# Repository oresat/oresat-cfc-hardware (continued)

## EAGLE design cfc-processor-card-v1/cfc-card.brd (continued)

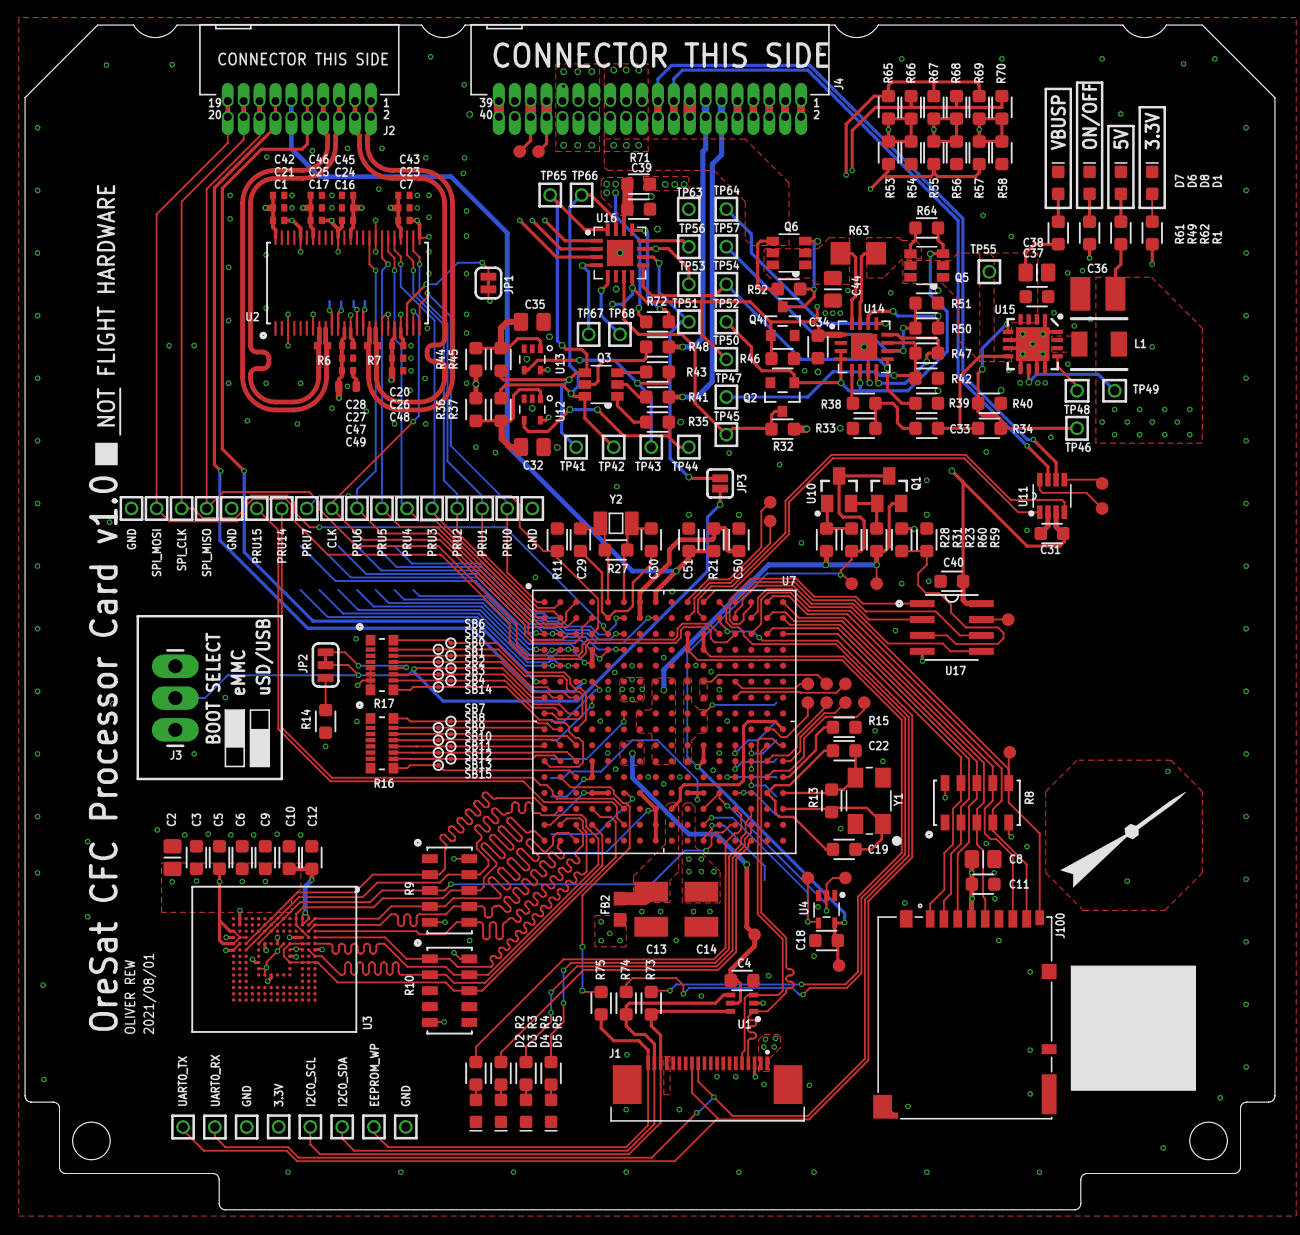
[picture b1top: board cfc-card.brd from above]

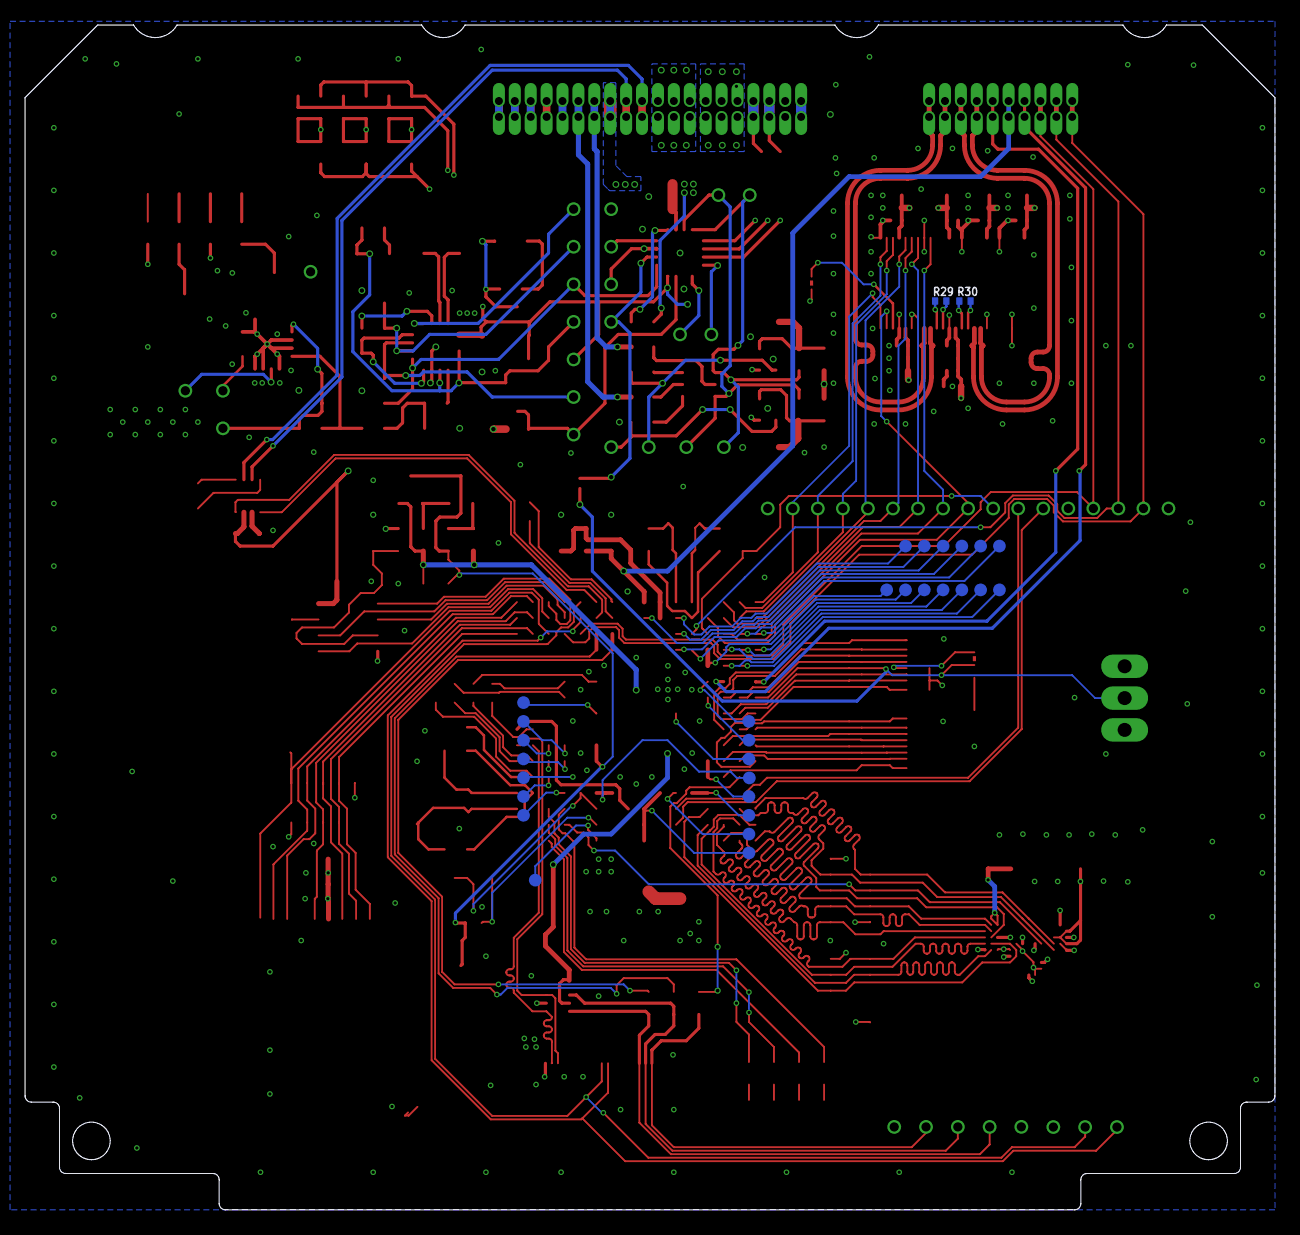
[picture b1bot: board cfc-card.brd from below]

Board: 4 copper layers, 99.8 x 94.6 mm, 274 parts (31 on the bottom side), 205 nets.

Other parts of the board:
U$2: CAMERA_BOARD_TOP_DIMS
U$3: PSAS_LOGO_10X10
U$4: ORESAT_ORIENTATION_COPPER

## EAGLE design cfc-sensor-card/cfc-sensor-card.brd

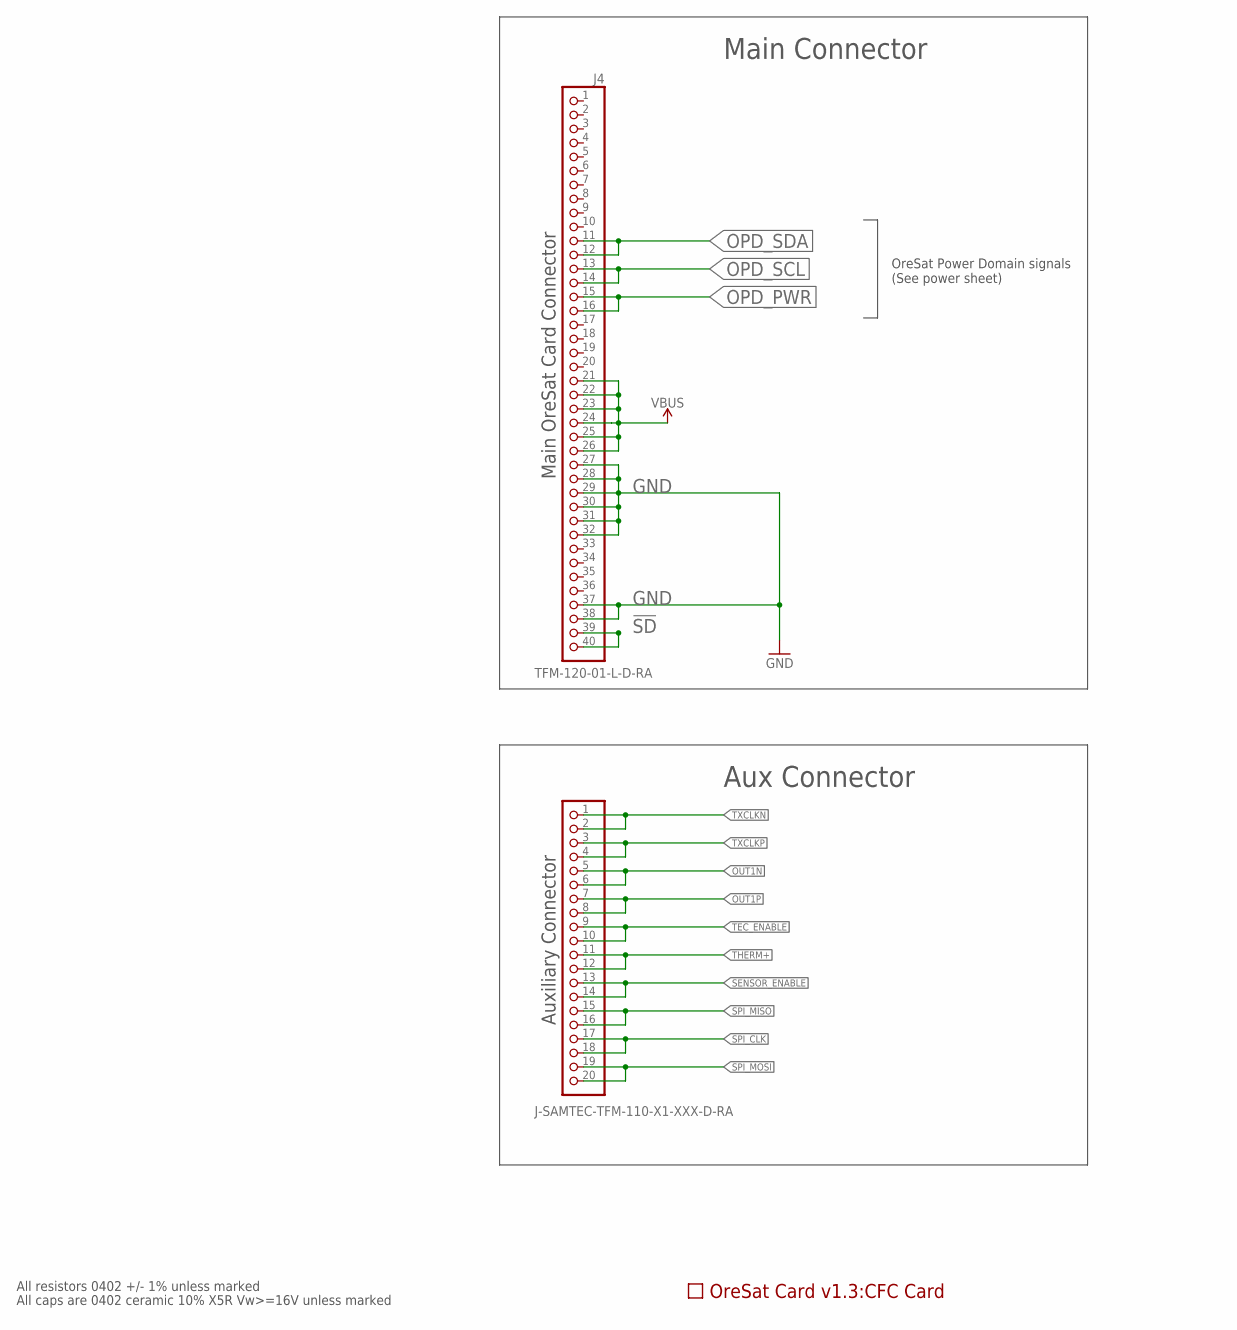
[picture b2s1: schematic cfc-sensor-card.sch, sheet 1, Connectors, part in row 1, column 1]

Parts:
J2: J-SAMTEC-TFM-110-X1-XXX-D-RA; MPN TFM-110-01-L-D-RA
J4: TFM-120-01-L-D-RA; J-SAMTEC-TFM-120-X1-XXX-D-RA
PCB1: ORESAT-CARD-V1.3-CFC
U$1: FLIGHMARKERNEW; FLIGHTMARKER_NEW_BOARDS

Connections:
!SD: J4.39, J4.40
GND: J4.27, J4.28, J4.29, J4.30, J4.31, J4.32, J4.37, J4.38; also elsewhere on the board
OPD_PWR: J4.15, J4.16; also elsewhere on the board
OPD_SCL: J4.13, J4.14; also elsewhere on the board
OPD_SDA: J4.11, J4.12; also elsewhere on the board
OUT1N: J2.5, J2.6; also elsewhere on the board
OUT1P: J2.7, J2.8; also elsewhere on the board
SENSOR_ENABLE: J2.13, J2.14; also elsewhere on the board
SPI_CLK: J2.17, J2.18; also elsewhere on the board
SPI_MISO: J2.15, J2.16; also elsewhere on the board
SPI_MOSI: J2.19, J2.20; also elsewhere on the board
TEC_ENABLE: J2.9, J2.10; also elsewhere on the board
THERM+: J2.11, J2.12; also elsewhere on the board
TXCLKN: J2.1, J2.2; also elsewhere on the board
TXCLKP: J2.3, J2.4; also elsewhere on the board
VBUS: J4.21, J4.22, J4.23, J4.24, J4.25, J4.26; also elsewhere on the board

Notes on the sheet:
OreSat Star Tracker: Connectors
1.2
All resistors 0402 +/- 1% unless marked
All caps are 0402 ceramic 10% X5R Vw>=16V unless marked
Main Connector
Main OreSat Card Connector
OreSat Power Domain signals (See power sheet)
Auxiliary Connector
Aux Connector

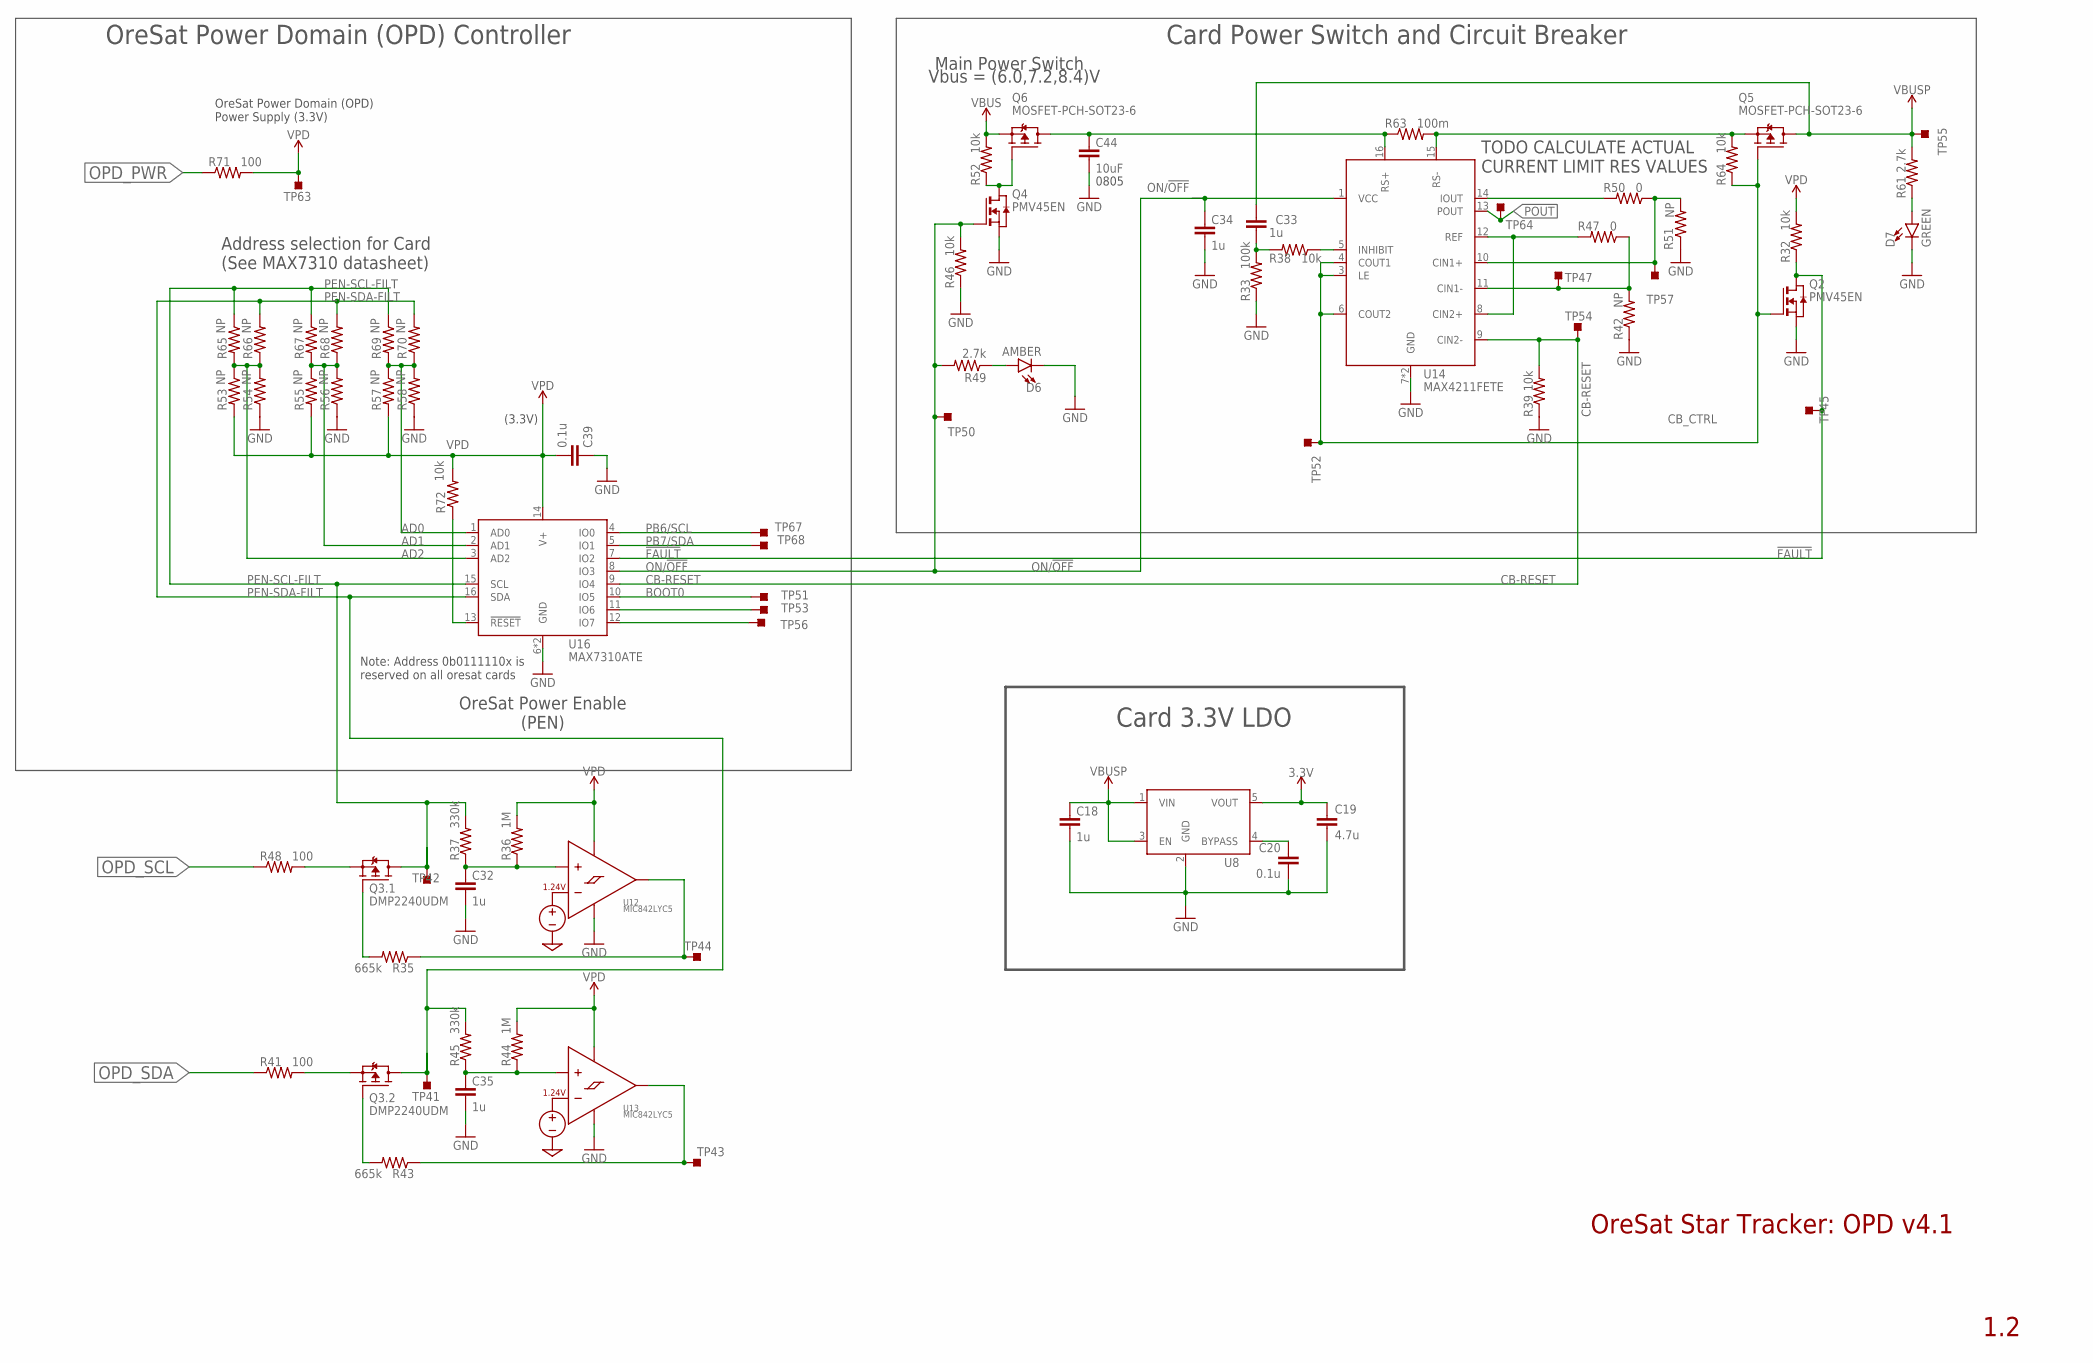
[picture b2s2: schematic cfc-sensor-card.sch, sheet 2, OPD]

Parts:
C18, C32, C33, C34, C35: 1u; .0603-B
C19: 4.7u; .0603-B
C20, C39: 0.1u; .0603-B
C44: 10uF; .0603-B
D6: AMBER; LED-0603
D7: GREEN; LED-0603
Q2, Q4: PMV45EN; SOT23; MPN PMV45EN2R
Q3: DMP2240UDM; SOT23-6
Q5, Q6: MOSFET-PCH-SOT23-6; SOT23-6; MPN DMP3050LVT-7
R32, R39, R46, R52, R64, R72: 10k; .0603-B
R33: 100k; .0603-B; MPN RC1005F6653CS
R35, R43: 665k; .0603-B
R36, R44: 1M; .0603-B
R37, R45: 330k; .0603-B
R38: 10k; .0603-B; MPN RC1005F6653CS
R41, R48, R71: 100; .0603-B
R42, R51, R53, R54, R55, R56, R57, R58, R65, R66, R67, R68, R69, R70: NP; .0603-B; MPN RC1005F6653CS
R47, R50: 0; .0603-B
R49, R61: 2.7k; .0603-B
R63: 100m; R1206
TP41, TP42, TP43, TP44, TP45, TP47, TP50, TP51, TP52, TP53, TP54, TP55, TP56, TP57, TP63, TP64, TP67, TP68: TEST-POINT_SMD-SMD-10SN; TESTPOINT_SMD-10SN
U8: LP2985AIM5-3.3_NOPB; SOT-23
U12, U13: MIC842LYC5; SC70-5
U14: MAX4211FETE; QFN65P400X400X80-17T210
U16: MAX7310ATE; QFN65P400X400X80-17T210; MPN MAX7310ATE

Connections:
3.3V: C19.1, U8.5 (VOUT); also elsewhere on the board
!FAULT: Q2.3 (D), R32.1, TP45.TP, U16.7 (IO2)
AD0: R57.1, R58.2, R69.2, R70.1, U16.1 (AD0)
AD1: R55.1, R56.2, R67.2, R68.1, U16.2 (AD1)
AD2: R53.1, R54.2, R65.2, R66.1, U16.3 (AD2)
BOOT0: TP51.TP, U16.10 (IO5)
CB-RESET: R39.2, TP54.TP, U14.9 (CIN2-), U16.9 (IO4)
CB_CTRL: Q2.1 (G), Q5.3 (G), R64.1, TP52.TP, U14.3 (LE), U14.4 (COUT1), U14.6 (COUT2)
GND: C18.2, C19.2, C20.2, C32.2, C34.2, C35.2, C39.1, C44.2, D6.C, D7.C, Q2.2 (S), Q4.2 (S), R33.1, R39.1, R42.1, R46.1, R51.1, R54.1, R56.1, R58.1, U8.2 (GND), U12.2 (GND), U13.2 (GND), U14.7 (GND), U14.EPAD (GND), U16.6 (GND), U16.EPAD (GND); also elsewhere on the board
IOUT: R50.2, U14.14 (IOUT)
unnamed: C20.1, U8.4 (BYPASS)
unnamed: C32.1, R36.1, R37.1, U12.1 (INP)
unnamed: R35.1, TP44.TP, U12.4 (OUT)
unnamed: TP56.TP, U16.12 (IO7)
unnamed: C44.1, Q6.1 (D), Q6.2 (D), Q6.5 (D), Q6.6 (D), R63.1, U14.16 (RS+)
unnamed: Q5.4 (S), R63.2, R64.2, U14.15 (RS-)
unnamed: C35.1, R44.1, R45.1, U13.1 (INP)
unnamed: Q3.3 (G), R43.2
unnamed: Q3.1 (G), R35.2
unnamed: D7.A, R61.1
unnamed: TP53.TP, U16.11 (IO6)
unnamed: Q3.5 (S), R48.2
unnamed: D6.A, R49.1
unnamed: Q3.2 (S), R41.2
unnamed: R43.1, TP43.TP, U13.4 (OUT)
unnamed: R72.1, U16.13 (!RESET)
unnamed: Q4.3 (D), Q6.3 (G), R52.1
unnamed: R50.1, R51.2, TP57.TP, U14.10 (CIN1+)
unnamed: R42.2, R47.1, TP47.TP, U14.11 (CIN1-)
unnamed: R47.2, U14.8 (CIN2+), U14.12 (REF)
unnamed: C33.1, R33.2, R38.2
unnamed: R38.1, U14.5 (INHIBIT)
ON/!OFF: C34.1, Q4.1 (G), R46.2, R49.2, TP50.TP, U14.1 (VCC), U16.8 (IO3)
OPD_PWR: R71.1; also elsewhere on the board
OPD_SCL: R48.1; also elsewhere on the board
OPD_SDA: R41.1; also elsewhere on the board
PB6/SCL: TP67.TP, U16.4 (IO0)
PB7/SDA: TP68.TP, U16.5 (IO1)
PEN-SCL-FILT: Q3.6 (D), R37.2, R65.1, R67.1, R69.1, TP42.TP, U16.15 (SCL)
PEN-SDA-FILT: Q3.4 (D), R45.2, R66.2, R68.2, R70.2, TP41.TP, U16.16 (SDA)
POUT: TP64.TP, U14.13 (POUT)
VBUS: Q6.4 (S), R52.2; also elsewhere on the board
VBUSP: C18.1, C33.2, Q5.1 (D), Q5.2 (D), Q5.5 (D), Q5.6 (D), R61.2, TP55.TP, U8.1 (VIN), U8.3 (EN); also elsewhere on the board
VPD: C39.2, R32.2, R36.2, R44.2, R53.2, R55.2, R57.2, R71.2, R72.2, TP63.TP, U12.5 (VDD), U13.5 (VDD), U16.14 (V+)

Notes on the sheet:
1.2
Main Power Switch
OreSat Power Enable (PEN)
Address selection for Card (See MAX7310 datasheet)
(3.3V)
Vbus = (6.0,7.2,8.4)V
OreSat Power Domain (OPD) Power Supply (3.3V)
OreSat Power Domain (OPD) Controller
Card Power Switch and Circuit Breaker
Note: Address 0b0111110x is reserved on all oresat cards
0805
OreSat Star Tracker: OPD v4.1
Card 3.3V LDO
TODO CALCULATE ACTUAL CURRENT LIMIT RES VALUES

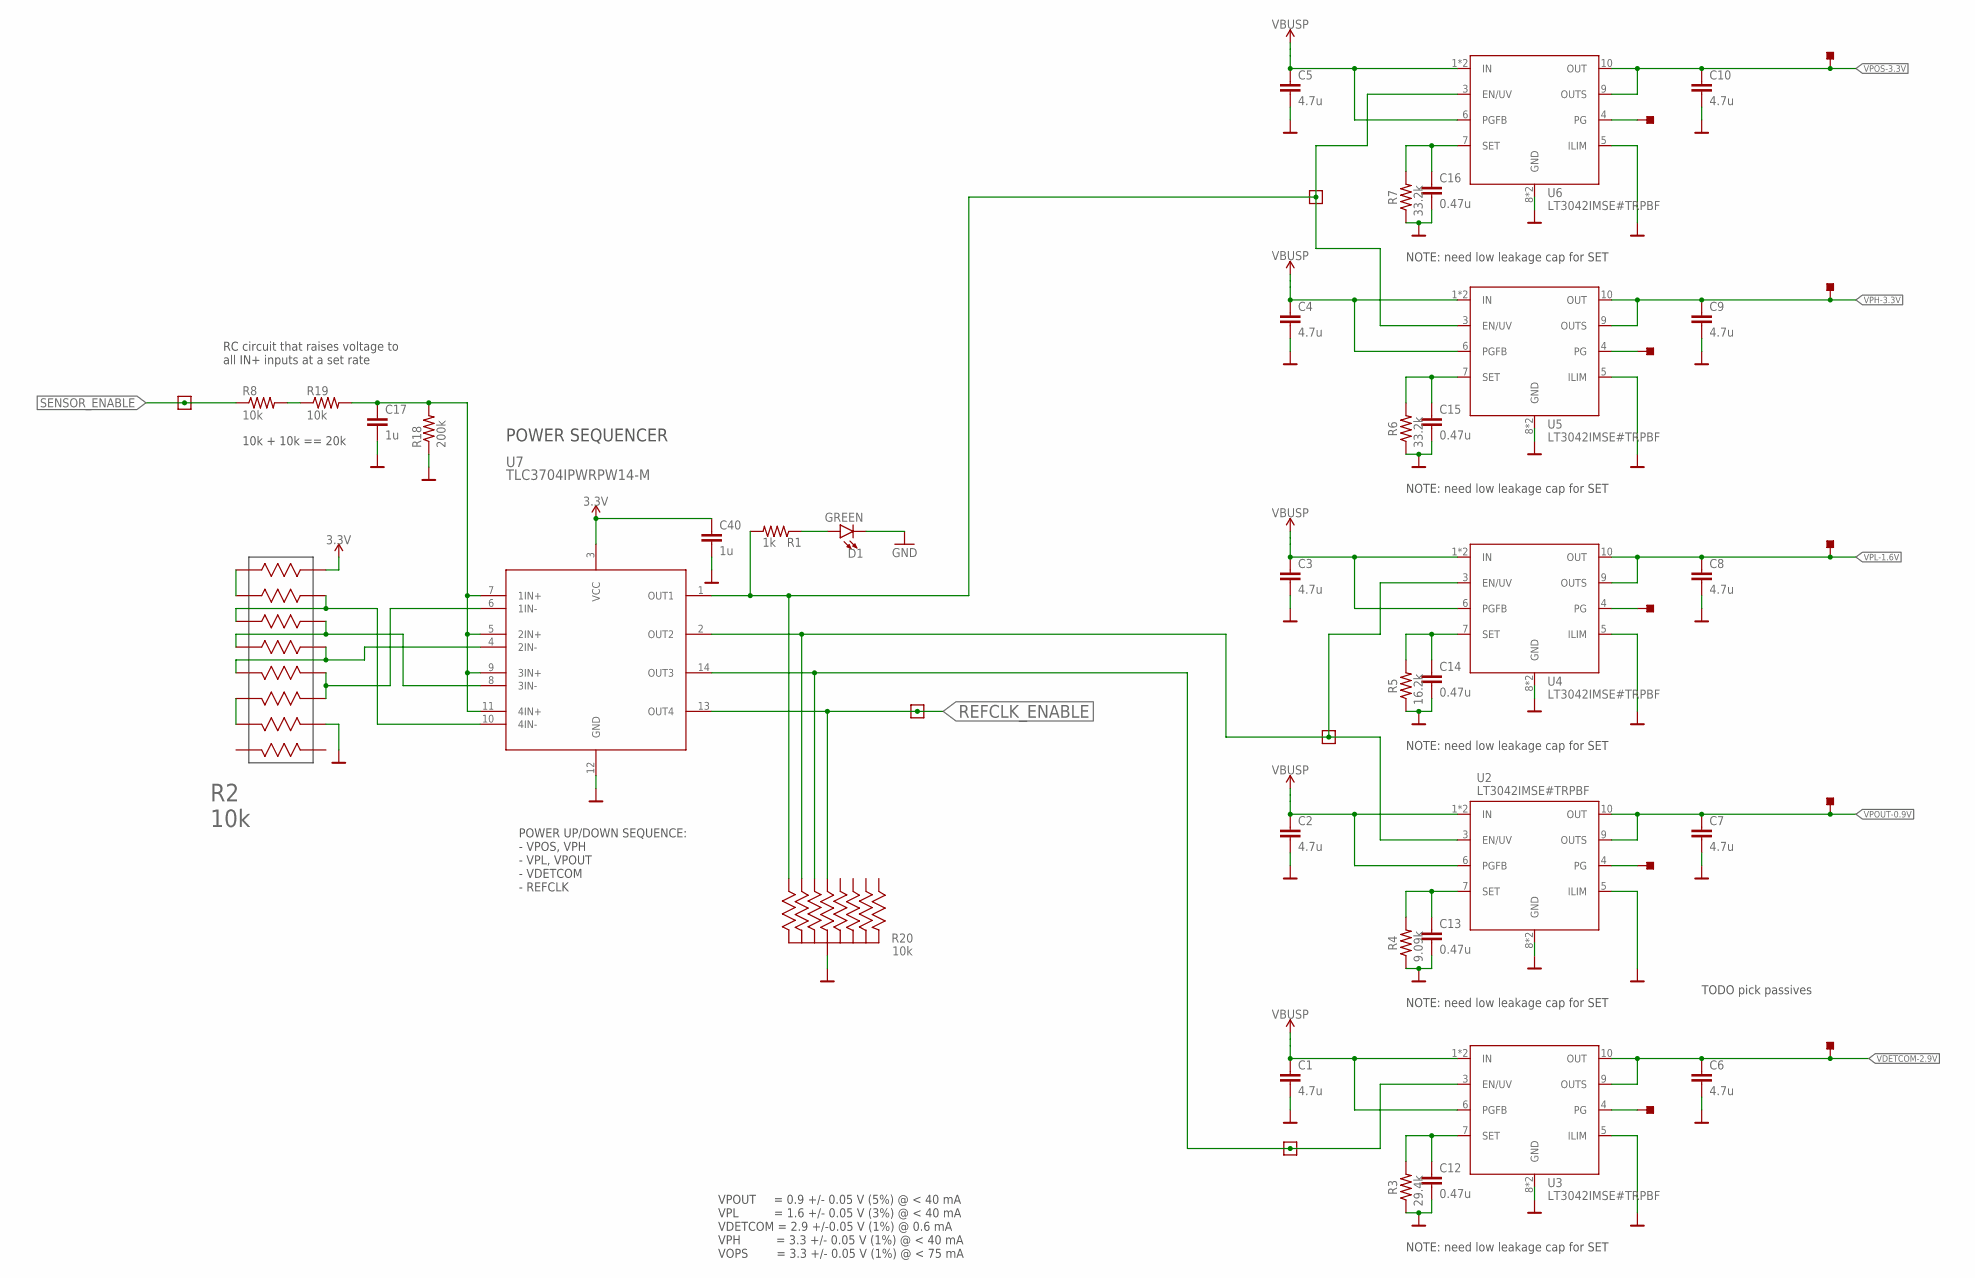
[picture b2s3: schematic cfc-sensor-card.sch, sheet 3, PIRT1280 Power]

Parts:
C1, C2, C3, C4, C5, C6, C7, C8, C9, C10: 4.7u; .0603-B
C12, C13, C14, C15, C16: 0.47u; .0603-B
C17, C40: 1u; .0603-B
D1: GREEN; LED-0603; MANUFACTURER_PART_NUMBER 150060VS55040; DIGI-KEY_PART_NUMBER 732-12017-1-ND
R1: 1k; .0603-B
R2: 10k; RES_EXB2HV
R3: 29.4k; .0603-B
R4: 9.09k; .0603-B
R5: 16.2k; .0603-B
R6, R7: 33.2k; .0603-B
R8, R19: 10k; .0603-B
R18: 200k; .0603-B
R20: 10k; ARRAY_EXBA-M; MPN EXB-A10P103J
TP1, TP16, TP18, TP27, TP39: TEST-POINT-LARGE-SQUARE; 1X01
TP2, TP5, TP8, TP11, TP14, TP22, TP23, TP24, TP25, TP26: TEST-POINT_SMD-SMD-10SN; TESTPOINT_SMD-10SN
U2, U3, U4, U5, U6: LT3042IMSE#TRPBF; SOP50P490X110-11N
U7: TLC3704IPWRPW14-M; 14-TSSOP

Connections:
3.3V: C40.1, R2.16, U7.3 (VCC); also elsewhere on the board
GND: C1.2, C2.2, C3.2, C4.2, C5.2, C6.2, C7.2, C8.2, C9.2, C10.2, C12.2, C13.2, C14.2, C15.2, C16.2, C17.2, C40.2, D1.C, R2.10, R3.1, R4.1, R5.1, R6.1, R7.1, R18.1, R20.5 (55), R20.10 (55), U2.5 (ILIM), U2.8 (GND), U2.11 (GND), U3.5 (ILIM), U3.8 (GND), U3.11 (GND), U4.5 (ILIM), U4.8 (GND), U4.11 (GND), U5.5 (ILIM), U5.8 (GND), U5.11 (GND), U6.5 (ILIM), U6.8 (GND), U6.11 (GND), U7.12 (GND); also elsewhere on the board
unnamed: R1.2, R20.6 (66), TP16.1, U5.3 (EN/UV), U6.3 (EN/UV), U7.1 (OUT1)
unnamed: R8.2, R19.1
unnamed: R2.1, R2.2
unnamed: R2.3, R2.15, U7.10 (4IN-)
unnamed: R2.4, R2.14, U7.8 (3IN-)
unnamed: R2.5, R2.13, U7.4 (2IN-)
unnamed: R2.6, R2.7
unnamed: C17.1, R18.2, R19.2, U7.5 (2IN+), U7.7 (1IN+), U7.9 (3IN+), U7.11 (4IN+)
unnamed: R20.7 (77), TP1.1, U3.3 (EN/UV), U7.14 (OUT3)
unnamed: D1.A, R1.1
unnamed: TP5.TP, U2.4 (PG)
unnamed: C13.1, R4.2, U2.7 (SET)
unnamed: TP2.TP, U3.4 (PG)
unnamed: C12.1, R3.2, U3.7 (SET)
unnamed: TP14.TP, U6.4 (PG)
unnamed: C16.1, R7.2, U6.7 (SET)
unnamed: TP11.TP, U5.4 (PG)
unnamed: C15.1, R6.2, U5.7 (SET)
unnamed: R20.4 (44), TP18.1, U2.3 (EN/UV), U4.3 (EN/UV), U7.2 (OUT2)
unnamed: TP8.TP, U4.4 (PG)
unnamed: C14.1, R5.2, U4.7 (SET)
unnamed: R2.11, R2.12, U7.6 (1IN-)
REFCLK_ENABLE: R20.3 (33), TP27.1, U7.13 (OUT4); also elsewhere on the board
SENSOR_ENABLE: R8.1, TP39.1; also elsewhere on the board
VBUSP: C1.1, C2.1, C3.1, C4.1, C5.1, U2.1 (IN), U2.2 (IN), U2.6 (PGFB), U3.1 (IN), U3.2 (IN), U3.6 (PGFB), U4.1 (IN), U4.2 (IN), U4.6 (PGFB), U5.1 (IN), U5.2 (IN), U5.6 (PGFB), U6.1 (IN), U6.2 (IN), U6.6 (PGFB); also elsewhere on the board
VDETCOM-2.9V: C6.1, TP22.TP, U3.9 (OUTS), U3.10 (OUT); also elsewhere on the board
VPH-3.3V: C9.1, TP25.TP, U5.9 (OUTS), U5.10 (OUT); also elsewhere on the board
VPL-1.6V: C8.1, TP24.TP, U4.9 (OUTS), U4.10 (OUT); also elsewhere on the board
VPOS-3.3V: C10.1, TP26.TP, U6.9 (OUTS), U6.10 (OUT); also elsewhere on the board
VPOUT-0.9V: C7.1, TP23.TP, U2.9 (OUTS), U2.10 (OUT); also elsewhere on the board

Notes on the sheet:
VPOUT = 0.9 +/- 0.05 V (5%) @ < 40 mA VPL = 1.6 +/- 0.05 V (3%) @ < 40 mA VDETCOM = 2.9 +/-0.05 V (1%) @ 0.6 mA VPH = 3.3 +/- 0.05 V (1%) @ < 40 mA VOPS = 3.3 +/- 0.05 V (1%) @ < 75 mA
NOTE: need low leakage cap for SET
TODO pick passives
POWER UP/DOWN SEQUENCE: - VPOS, VPH - VPL, VPOUT - VDETCOM - REFCLK
RC circuit that raises voltage to all IN+ inputs at a set rate
POWER SEQUENCER
10k + 10k == 20k

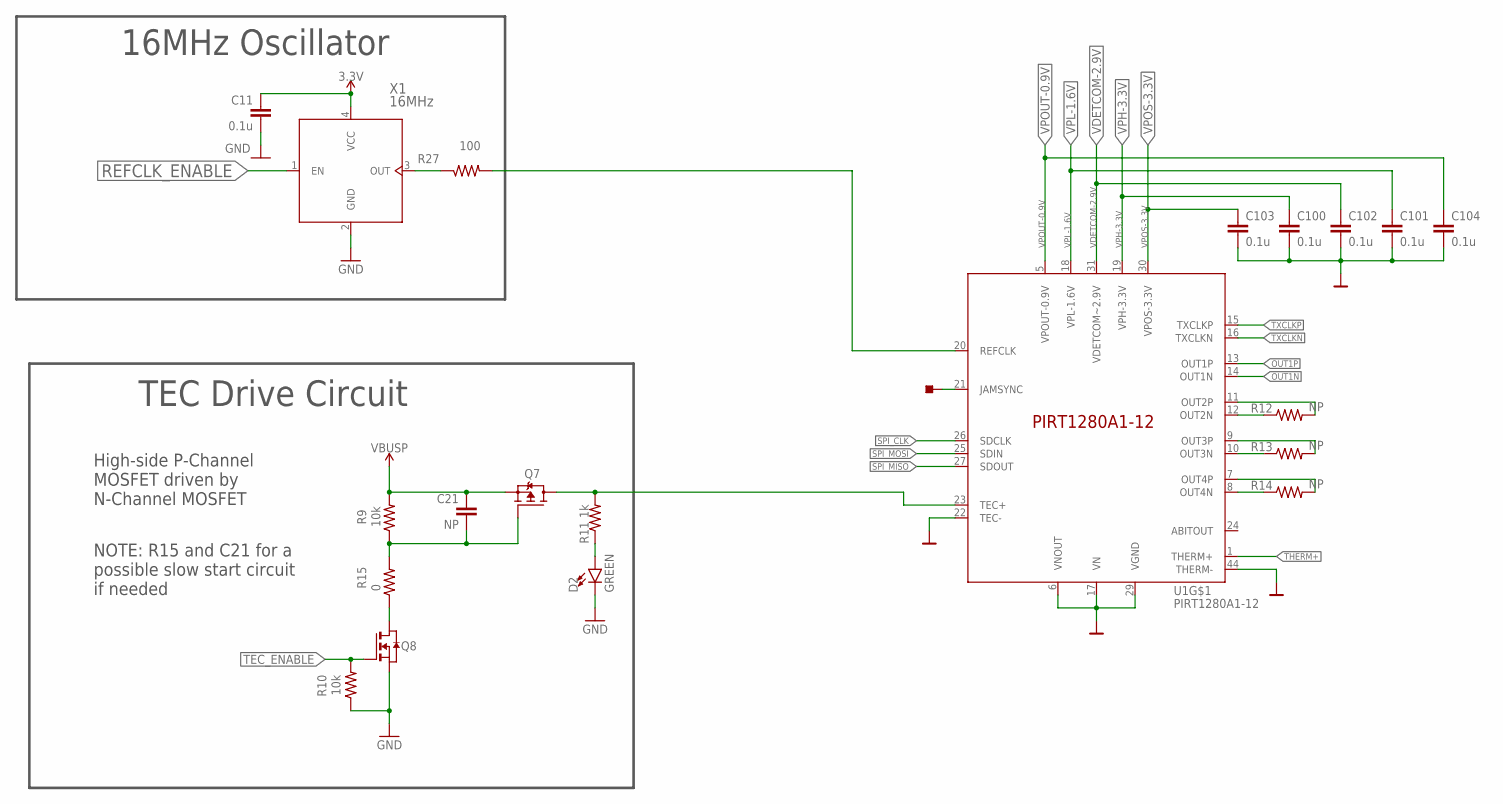
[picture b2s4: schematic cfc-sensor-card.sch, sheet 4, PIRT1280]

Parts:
C11, C100, C101, C102, C103, C104: 0.1u; .0603-B
C21: NP; .0603-B
D2: GREEN; LED-0603; MANUFACTURER_PART_NUMBER 150060VS55040; DIGI-KEY_PART_NUMBER 732-12017-1-ND
Q7: MOSFET-PCH-SOT23-6; SOT23-6; MPN DMP3050LVT-7
Q8: PMV45EN; SOT23; MPN PMV45EN2R
R9, R10: 10k; .0603-B
R11: 1k; .0603-B
R12, R13, R14: NP; .0402-C-NOSILK; MPN RC0201FR-07100RL
R15: 0; .0603-B
R27: 100; .0402-A; MPN RCA0402100RFKEDHP
TP40: TEST-POINT_SMD-SMD-10SN; TESTPOINT_SMD-10SN
U1: PIRT1280A1-12
X1: 16MHz; OSC_2.5X2.0

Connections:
3.3V: C11.1, X1.4 (VCC); also elsewhere on the board
GND: C11.2, C100.2, C101.2, C102.2, C103.2, C104.2, D2.C, Q8.2 (S), R10.1, U1.6 (VNOUT), U1.17 (VN), U1.22 (TEC-), U1.29 (VGND), U1.44 (THERM-), X1.2 (GND); also elsewhere on the board
unnamed: C21.2, Q7.3 (G), R9.1, R15.2
unnamed: R12.2, U1.11 (OUT2P)
unnamed: D2.A, R11.1
unnamed: R27.1, X1.3 (OUT)
unnamed: TP40.TP, U1.21 (JAMSYNC)
unnamed: R27.2, U1.20 (REFCLK)
unnamed: R12.1, U1.12 (OUT2N)
unnamed: R13.2, U1.9 (OUT3P)
unnamed: R13.1, U1.10 (OUT3N)
unnamed: R14.2, U1.7 (OUT4P)
unnamed: R14.1, U1.8 (OUT4N)
unnamed: Q8.3 (D), R15.1
OUT1N: U1.14 (OUT1N); also elsewhere on the board
OUT1P: U1.13 (OUT1P); also elsewhere on the board
REFCLK_ENABLE: X1.1 (EN); also elsewhere on the board
SPI_CLK: U1.26 (SDCLK); also elsewhere on the board
SPI_MISO: U1.27 (SDOUT); also elsewhere on the board
SPI_MOSI: U1.25 (SDIN); also elsewhere on the board
TEC+: Q7.1 (D), Q7.2 (D), Q7.5 (D), Q7.6 (D), R11.2, U1.23 (TEC+)
TEC_ENABLE: Q8.1 (G), R10.2; also elsewhere on the board
THERM+: U1.1 (THERM+); also elsewhere on the board
TXCLKN: U1.16 (TXCLKN); also elsewhere on the board
TXCLKP: U1.15 (TXCLKP); also elsewhere on the board
VBUSP: C21.1, Q7.4 (S), R9.2; also elsewhere on the board
VDETCOM-2.9V: C102.1, U1.31 (VDETCOM~2.9V); also elsewhere on the board
VPH-3.3V: C100.1, U1.19 (VPH-3.3V); also elsewhere on the board
VPL-1.6V: C101.1, U1.18 (VPL-1.6V); also elsewhere on the board
VPOS-3.3V: C103.1, U1.30 (VPOS-3.3V); also elsewhere on the board
VPOUT-0.9V: C104.1, U1.5 (VPOUT-0.9V); also elsewhere on the board

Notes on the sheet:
16MHz Oscillator
TEC Drive Circuit
High-side P-Channel MOSFET driven by N-Channel MOSFET
NOTE: R15 and C21 for a possible slow start circuit if needed

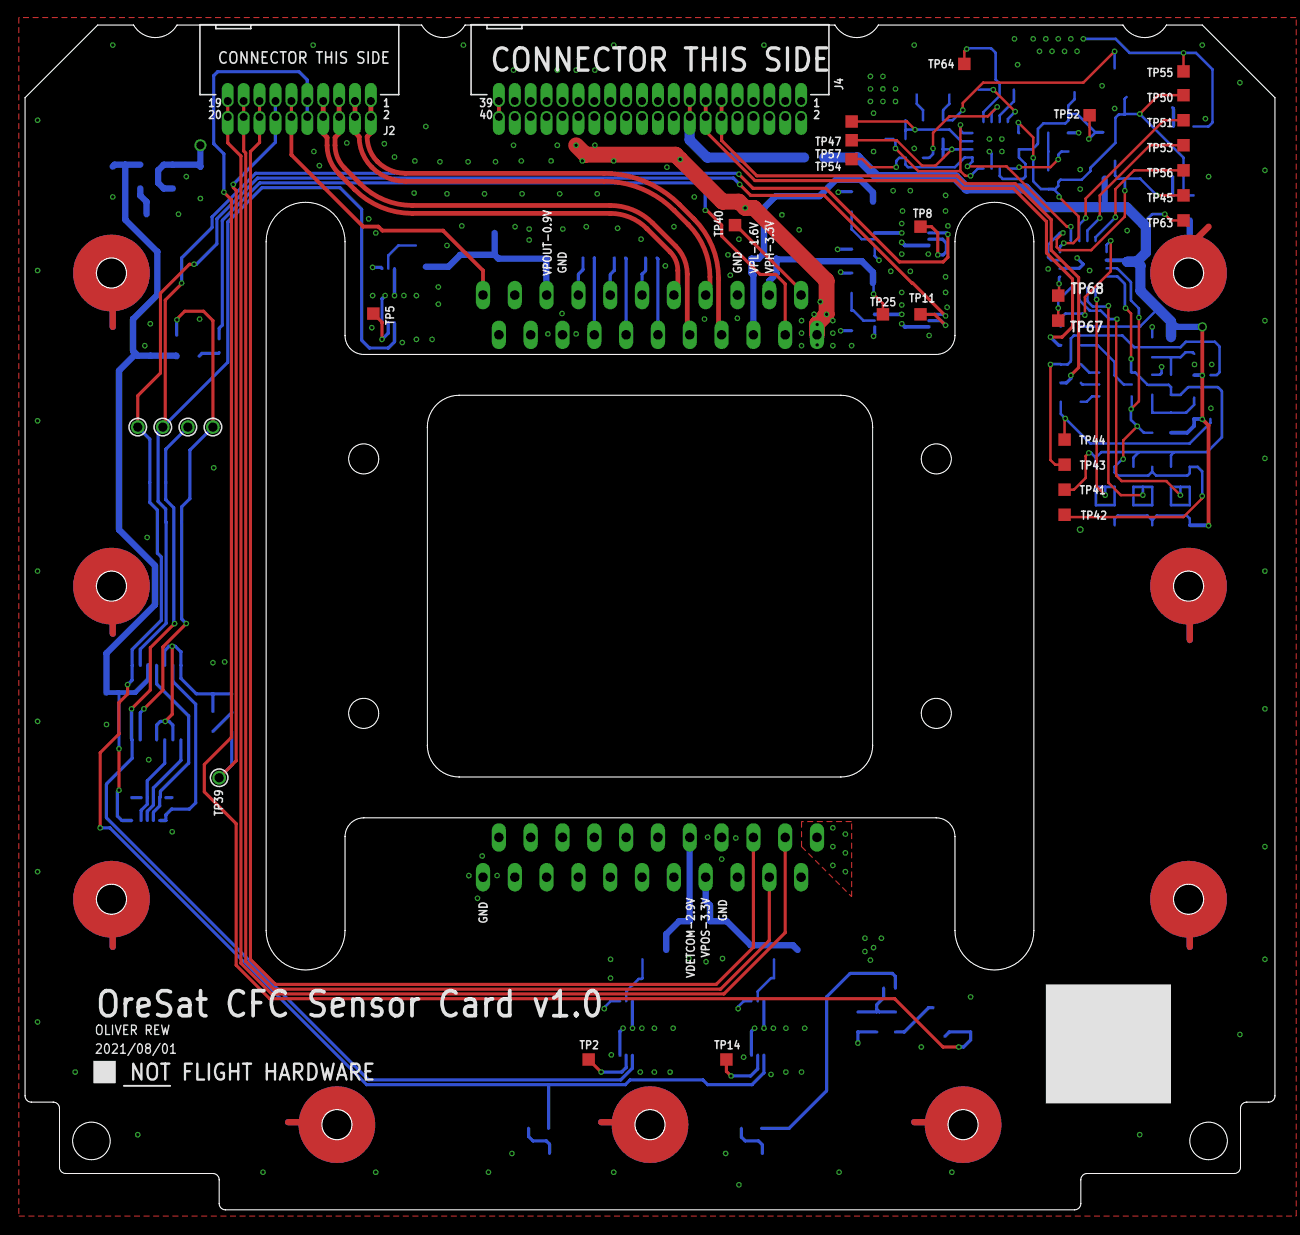
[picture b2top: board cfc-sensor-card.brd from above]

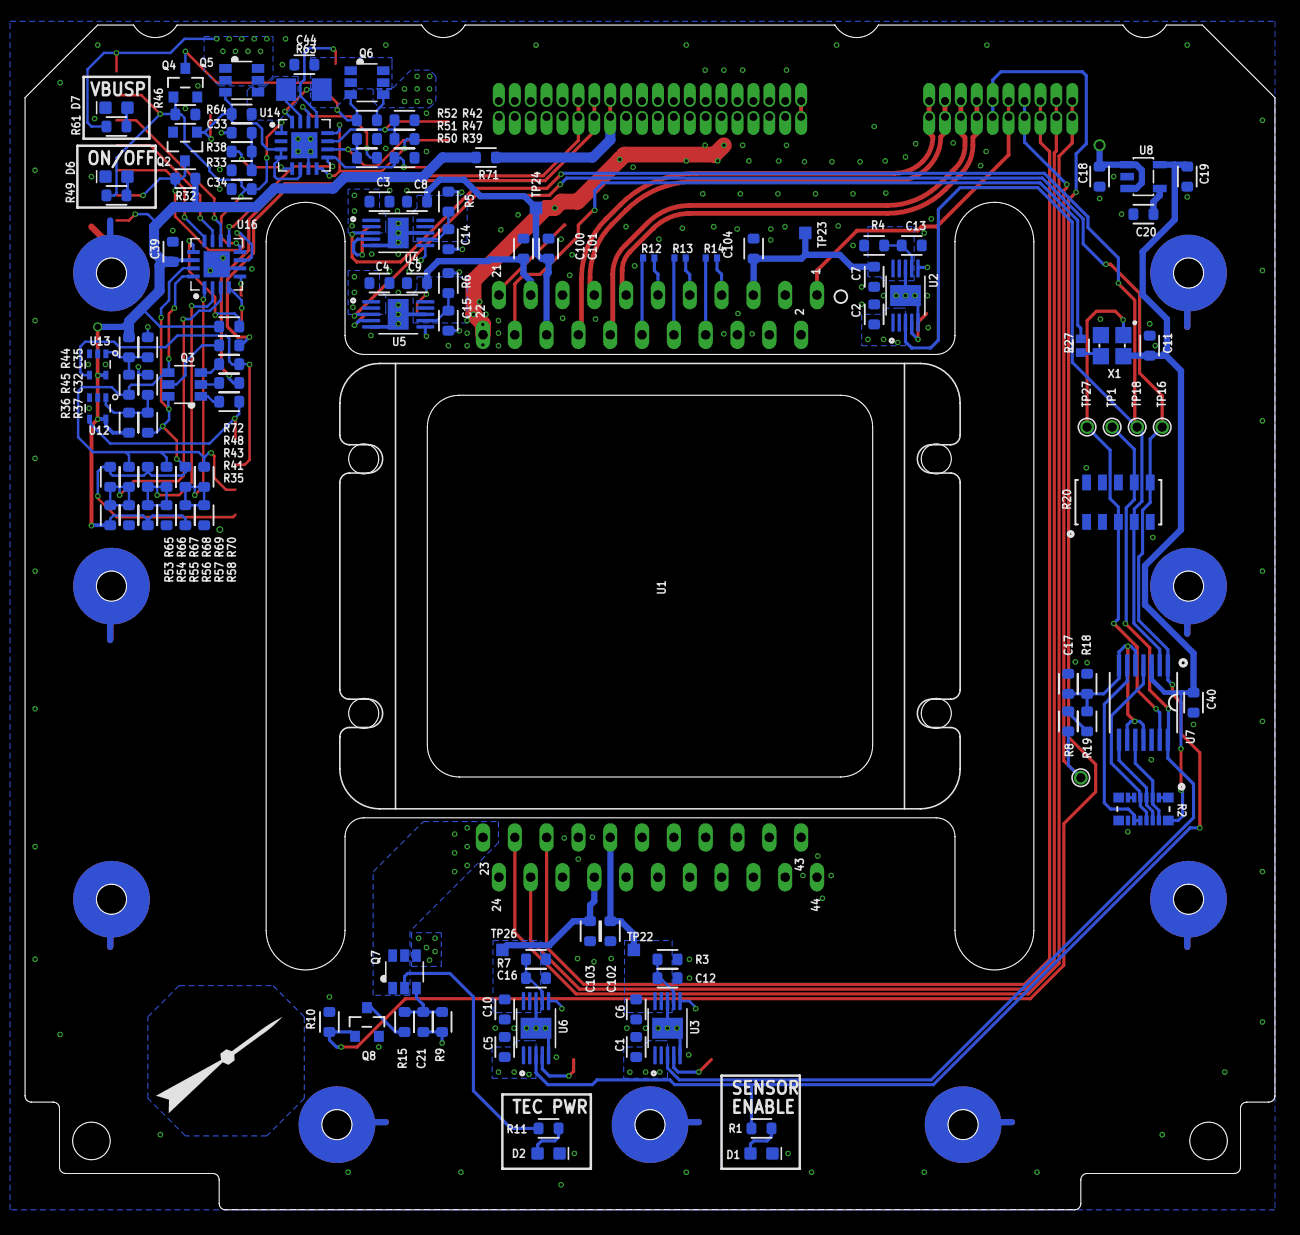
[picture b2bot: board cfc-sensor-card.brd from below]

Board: 4 copper layers, 99.8 x 94.6 mm, 152 parts (118 on the bottom side), 96 nets.

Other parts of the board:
U$2: ORESAT_ORIENTATION_COPPER
U$3: PSAS_LOGO_10X10
